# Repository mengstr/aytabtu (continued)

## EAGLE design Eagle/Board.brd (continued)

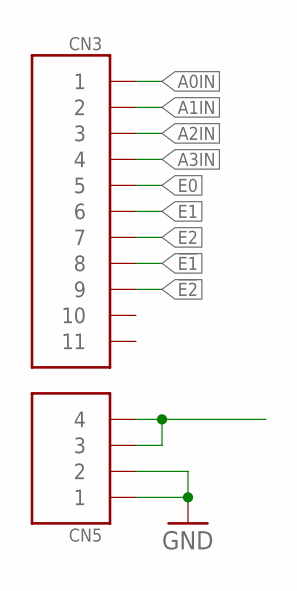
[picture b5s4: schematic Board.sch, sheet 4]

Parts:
CN3: HD11
CN5: HD4

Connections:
!E1: CN3.P$8 (8)
!E2: CN3.P$9 (9)
A0IN: CN3.P$1 (1); also elsewhere on the board
A1IN: CN3.P$2 (2); also elsewhere on the board
A2IN: CN3.P$3 (3); also elsewhere on the board
A3IN: CN3.P$4 (4)
E0: CN3.P$5 (5)
E1: CN3.P$6 (6)
E2: CN3.P$7 (7)
GND: CN5.P$1 (1), CN5.P$2 (2); also elsewhere on the board
unnamed: CN5.P$3 (3), CN5.P$4 (4)

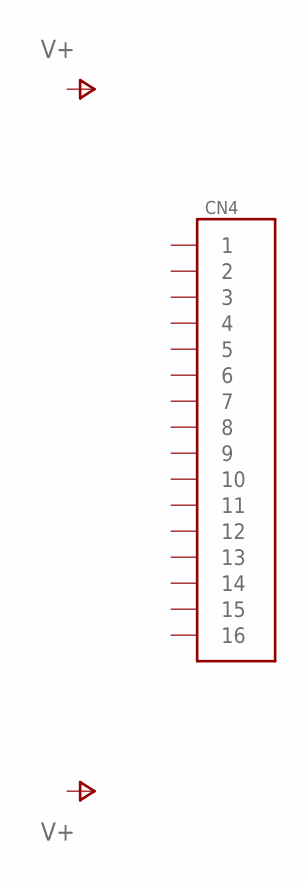
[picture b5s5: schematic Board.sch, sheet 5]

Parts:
CN4: HD16

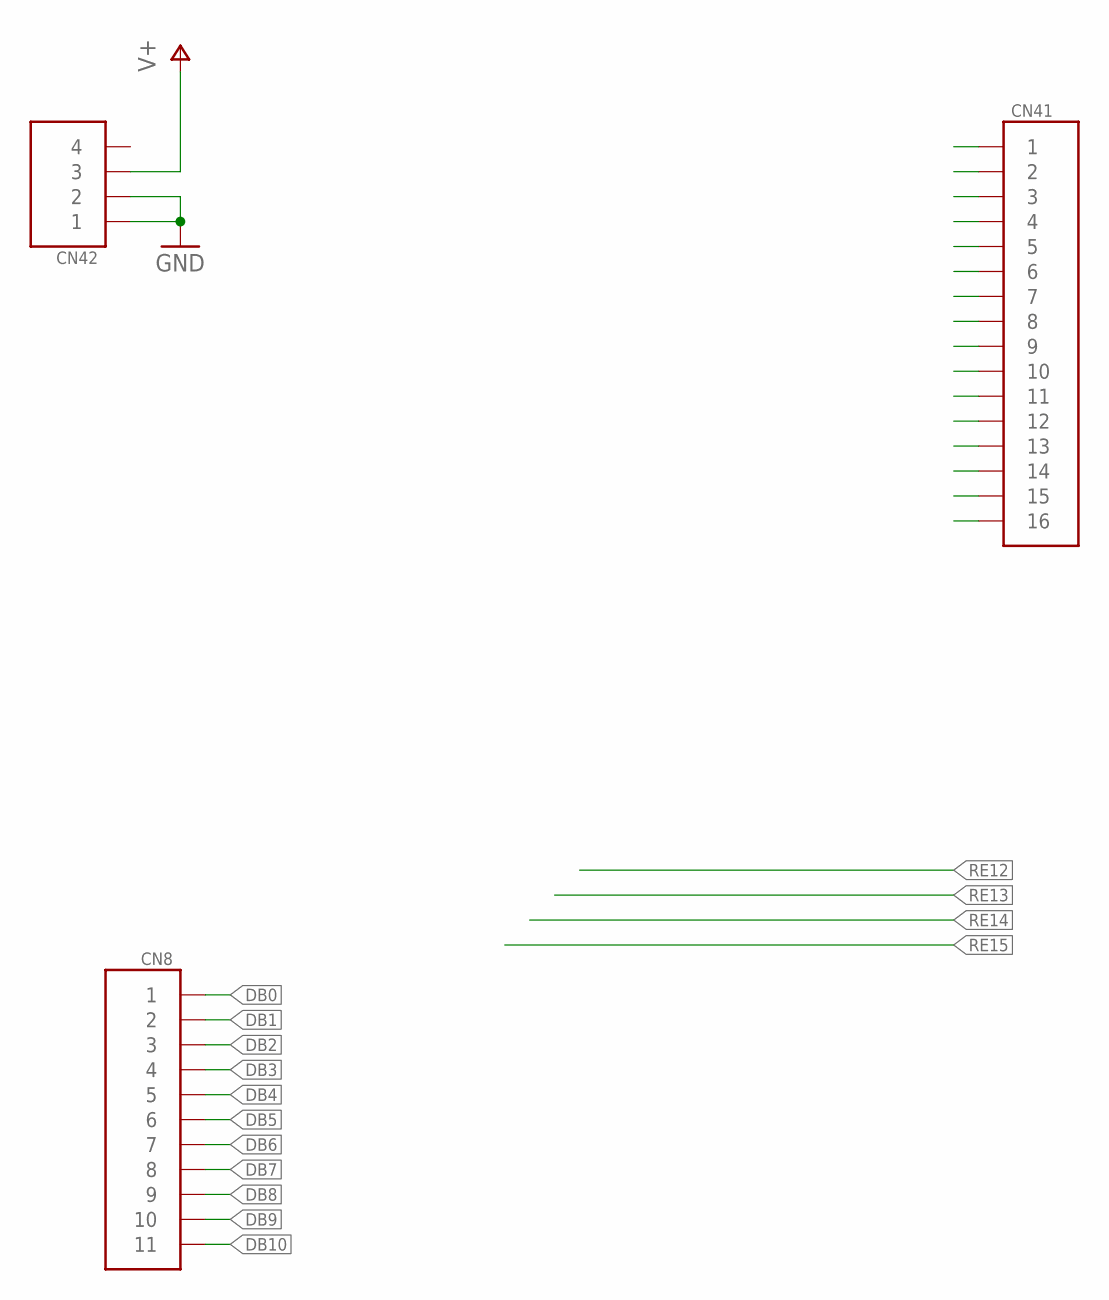
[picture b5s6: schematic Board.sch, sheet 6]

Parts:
CN8: HD11
CN41: HD16
CN42: HD4

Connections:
DB0: CN8.P$1 (1)
DB1: CN8.P$2 (2)
DB2: CN8.P$3 (3)
DB3: CN8.P$4 (4)
DB4: CN8.P$5 (5)
DB5: CN8.P$6 (6)
DB6: CN8.P$7 (7)
DB7: CN8.P$8 (8)
DB8: CN8.P$9 (9)
DB9: CN8.P$10 (10)
DB10: CN8.P$11 (11)
GND: CN42.P$1 (1), CN42.P$2 (2); also elsewhere on the board
SEL16: CN41.P$1 (1)
SEL17: CN41.P$2 (2)
SEL18: CN41.P$3 (3)
SEL19: CN41.P$4 (4)
SEL20: CN41.P$5 (5)
SEL21: CN41.P$6 (6)
SEL22: CN41.P$7 (7)
SEL23: CN41.P$8 (8)
SEL24: CN41.P$9 (9)
SEL25: CN41.P$10 (10)
SEL26: CN41.P$11 (11)
SEL27: CN41.P$12 (12)
SEL28: CN41.P$13 (13)
SEL29: CN41.P$16 (16)
SEL30: CN41.P$15 (15)
SEL31: CN41.P$14 (14)
V+: CN42.P$3 (3); also elsewhere on the board

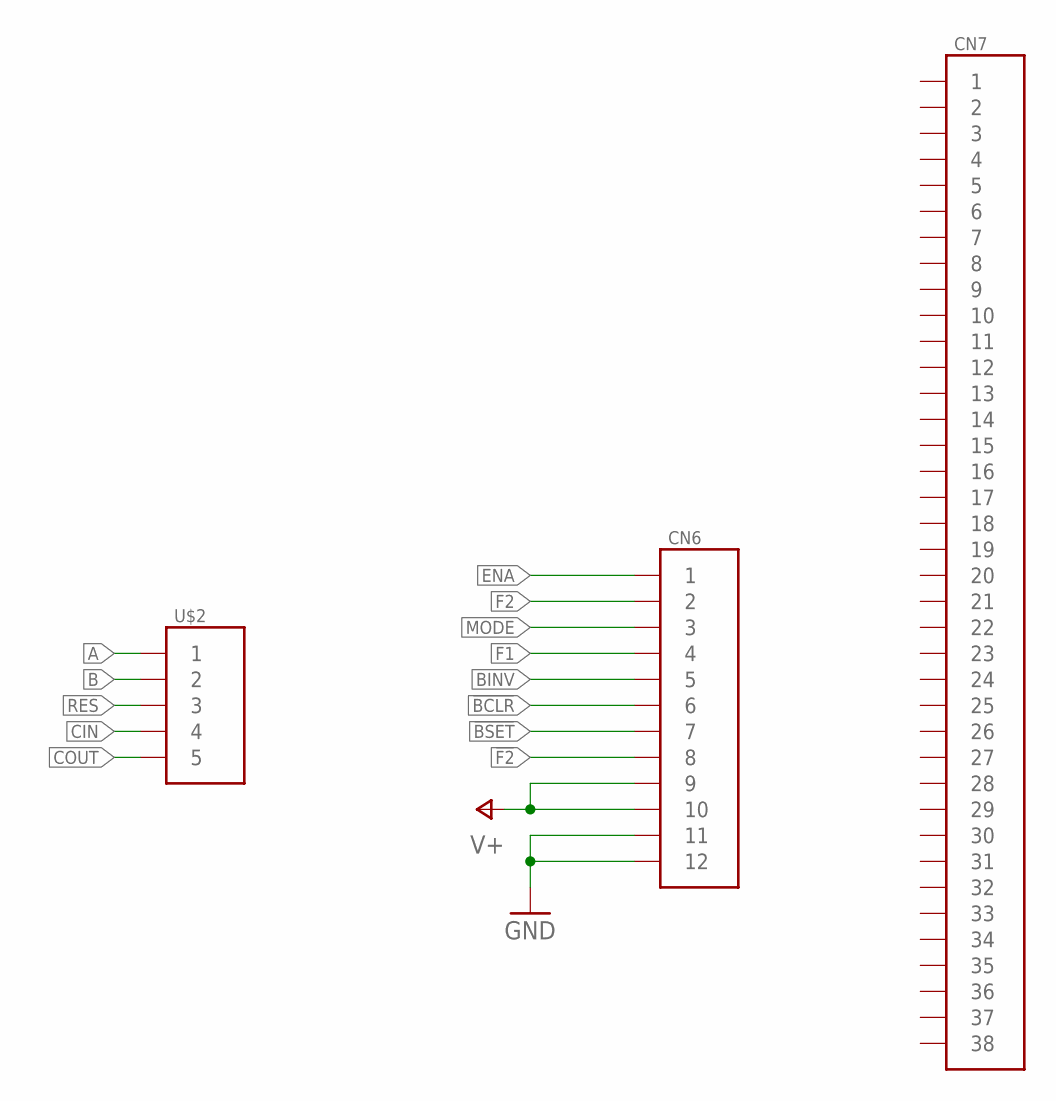
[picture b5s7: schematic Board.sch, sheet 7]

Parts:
CN6: HD12
CN7: HD38-HP; HD38-HOLEPAD
U$2: HD5CN; HD5

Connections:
!BCLR: CN6.P$6 (6)
!BSET: CN6.P$7 (7)
!F2: CN6.P$8 (8)
A: U$2.P$1 (1)
B: U$2.P$2 (2)
BINV: CN6.P$5 (5)
CIN: U$2.P$4 (4)
COUT: U$2.P$5 (5)
ENA: CN6.P$1 (1)
F1: CN6.P$4 (4)
F2: CN6.P$2 (2)
GND: CN6.P$11 (11), CN6.P$12 (12); also elsewhere on the board
MODE: CN6.P$3 (3)
RES: U$2.P$3 (3)
V+: CN6.P$9 (9), CN6.P$10 (10); also elsewhere on the board

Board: 2 copper layers, 15 parts (0 on the bottom side), 8 nets, no tracks yet.

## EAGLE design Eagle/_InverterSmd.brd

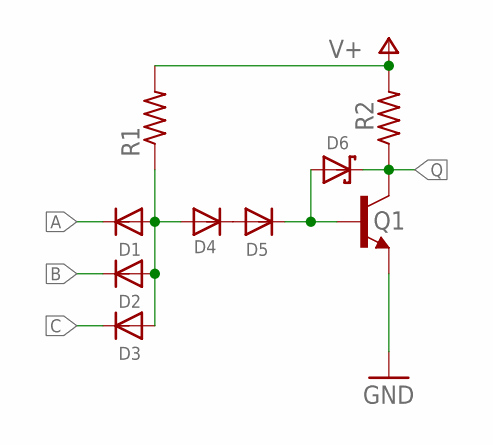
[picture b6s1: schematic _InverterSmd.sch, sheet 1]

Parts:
D1, D2, D3, D4, D5: DIODE-SOD323; SOD323F
D6: SCHOTTKYSOT323; SOT23
Q1: BC547-SOT23; SOT23
R1: 470; R0805
R2: 150; R0805

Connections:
A: D1.C
B: D2.C
C: D3.C
GND: Q1.2 (E)
unnamed: D1.A, D2.A, D3.A, D4.A, R1.1
unnamed: D5.C, D6.1 (A), Q1.1 (B)
unnamed: D4.C, D5.A
Q: D6.3 (C), Q1.3 (C), R2.1
V+: R1.2, R2.2

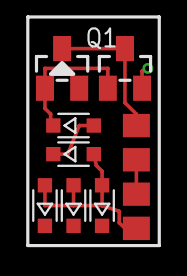
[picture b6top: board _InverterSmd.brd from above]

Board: 2 copper layers, 9 parts (0 on the bottom side), 5 nets.

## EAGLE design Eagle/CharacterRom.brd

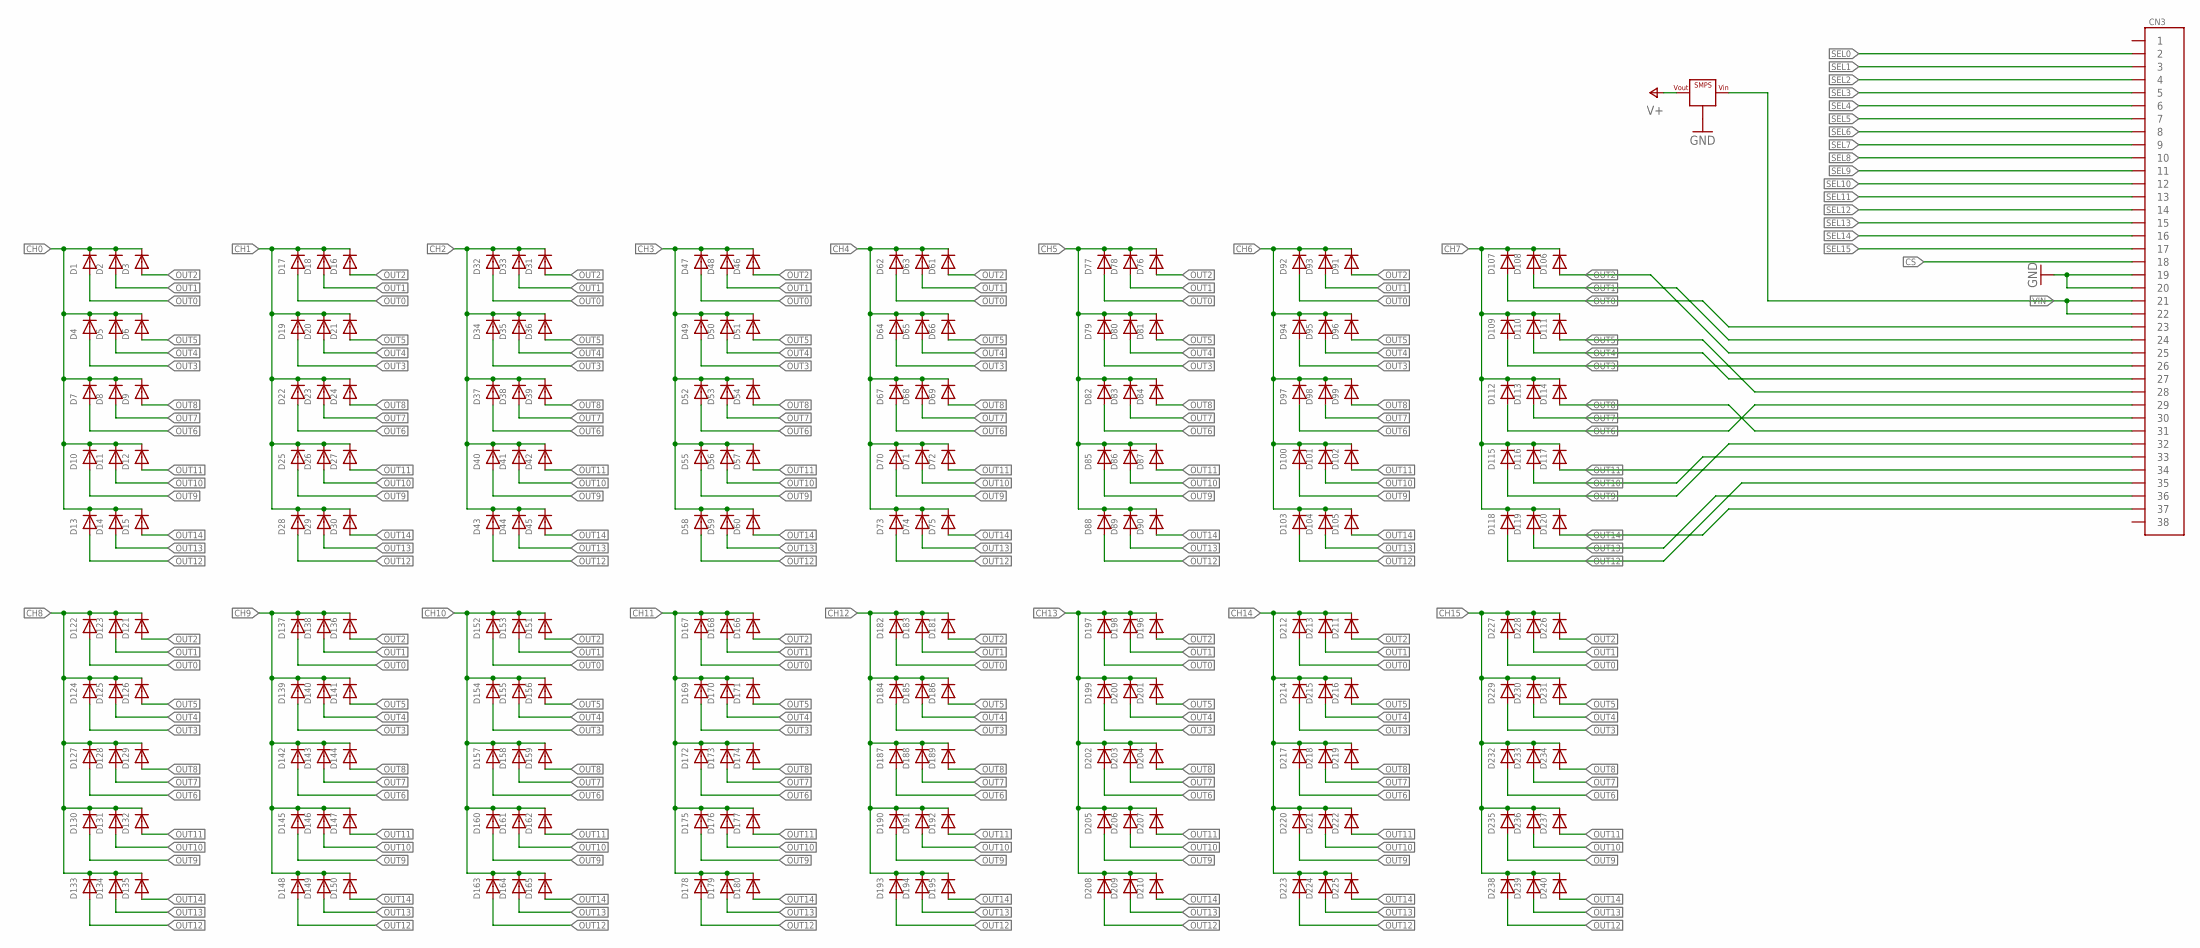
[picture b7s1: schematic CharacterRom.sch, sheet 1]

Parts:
CN3: HD38-HP; HD38-HOLEPAD
D1, D2, D3, D4, D5, D6, D7, D8, D9, D10, D11, D12, D13, D14, D15, D16, D17, D18, D19, D20, D21, D22, D23, D24, D25, D26, D27, D28, D29, D30, D31, D32, D33, D34, D35, D36, D37, D38, D39, D40, D41, D42, D43, D44, D45, D46, D47, D48, D49, D50, D51, D52, D53, D54, D55, D56, D57, D58, D59, D60, D61, D62, D63, D64, D65, D66, D67, D68, D69, D70, D71, D72, D73, D74, D75, D76, D77, D78, D79, D80, D81, D82, D83, D84, D85, D86, D87, D88, D89, D90, D91, D92, D93, D94, D95, D96, D97, D98, D99, D100, D101, D102, D103, D104, D105, D106, D107, D108, D109, D110, D111, D112, D113, D114, D115, D116, D117, D118, D119, D120, D121, D122, D123, D124, D125, D126, D127, D128, D129, D130, D131, D132, D133, D134, D135, D136, D137, D138, D139, D140, D141, D142, D143, D144, D145, D146, D147, D148, D149, D150, D151, D152, D153, D154, D155, D156, D157, D158, D159, D160, D161, D162, D163, D164, D165, D166, D167, D168, D169, D170, D171, D172, D173, D174, D175, D176, D177, D178, D179, D180, D181, D182, D183, D184, D185, D186, D187, D188, D189, D190, D191, D192, D193, D194, D195, D196, D197, D198, D199, D200, D201, D202, D203, D204, D205, D206, D207, D208, D209, D210, D211, D212, D213, D214, D215, D216, D217, D218, D219, D220, D221, D222, D223, D224, D225, D226, D227, D228, D229, D230, D231, D232, D233, D234, D235, D236, D237, D238, D239, D240: DIODESOD-323F; SOD-323F
VR1: SMPS; BUCK1722

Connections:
CH0: D1.C, D2.C, D3.C, D4.C, D5.C, D6.C, D7.C, D8.C, D9.C, D10.C, D11.C, D12.C, D13.C, D14.C, D15.C; also elsewhere on the board
CH1: D16.C, D17.C, D18.C, D19.C, D20.C, D21.C, D22.C, D23.C, D24.C, D25.C, D26.C, D27.C, D28.C, D29.C, D30.C; also elsewhere on the board
CH2: D31.C, D32.C, D33.C, D34.C, D35.C, D36.C, D37.C, D38.C, D39.C, D40.C, D41.C, D42.C, D43.C, D44.C, D45.C; also elsewhere on the board
CH3: D46.C, D47.C, D48.C, D49.C, D50.C, D51.C, D52.C, D53.C, D54.C, D55.C, D56.C, D57.C, D58.C, D59.C, D60.C; also elsewhere on the board
CH4: D61.C, D62.C, D63.C, D64.C, D65.C, D66.C, D67.C, D68.C, D69.C, D70.C, D71.C, D72.C, D73.C, D74.C, D75.C; also elsewhere on the board
CH5: D76.C, D77.C, D78.C, D79.C, D80.C, D81.C, D82.C, D83.C, D84.C, D85.C, D86.C, D87.C, D88.C, D89.C, D90.C; also elsewhere on the board
CH6: D91.C, D92.C, D93.C, D94.C, D95.C, D96.C, D97.C, D98.C, D99.C, D100.C, D101.C, D102.C, D103.C, D104.C, D105.C; also elsewhere on the board
CH7: D106.C, D107.C, D108.C, D109.C, D110.C, D111.C, D112.C, D113.C, D114.C, D115.C, D116.C, D117.C, D118.C, D119.C, D120.C; also elsewhere on the board
CH8: D121.C, D122.C, D123.C, D124.C, D125.C, D126.C, D127.C, D128.C, D129.C, D130.C, D131.C, D132.C, D133.C, D134.C, D135.C; also elsewhere on the board
CH9: D136.C, D137.C, D138.C, D139.C, D140.C, D141.C, D142.C, D143.C, D144.C, D145.C, D146.C, D147.C, D148.C, D149.C, D150.C; also elsewhere on the board
CH10: D151.C, D152.C, D153.C, D154.C, D155.C, D156.C, D157.C, D158.C, D159.C, D160.C, D161.C, D162.C, D163.C, D164.C, D165.C; also elsewhere on the board
CH11: D166.C, D167.C, D168.C, D169.C, D170.C, D171.C, D172.C, D173.C, D174.C, D175.C, D176.C, D177.C, D178.C, D179.C, D180.C; also elsewhere on the board
CH12: D181.C, D182.C, D183.C, D184.C, D185.C, D186.C, D187.C, D188.C, D189.C, D190.C, D191.C, D192.C, D193.C, D194.C, D195.C; also elsewhere on the board
CH13: D196.C, D197.C, D198.C, D199.C, D200.C, D201.C, D202.C, D203.C, D204.C, D205.C, D206.C, D207.C, D208.C, D209.C, D210.C; also elsewhere on the board
CH14: D211.C, D212.C, D213.C, D214.C, D215.C, D216.C, D217.C, D218.C, D219.C, D220.C, D221.C, D222.C, D223.C, D224.C, D225.C; also elsewhere on the board
CH15: D226.C, D227.C, D228.C, D229.C, D230.C, D231.C, D232.C, D233.C, D234.C, D235.C, D236.C, D237.C, D238.C, D239.C, D240.C; also elsewhere on the board
CS: CN3.P18@1 (18), CN3.P18@2 (18); also elsewhere on the board
GND: CN3.P19@1 (19), CN3.P19@2 (19), CN3.P20@1 (20), CN3.P20@2 (20), VR1.GND@1 (GND), VR1.GND@2 (GND), VR1.GND@3 (GND), VR1.GND@4 (GND); also elsewhere on the board
OUT0: CN3.P23@1 (23), CN3.P23@2 (23), D1.A, D17.A, D32.A, D47.A, D62.A, D77.A, D92.A, D107.A, D122.A, D137.A, D152.A, D167.A, D182.A, D197.A, D212.A, D227.A
OUT1: CN3.P24@1 (24), CN3.P24@2 (24), D2.A, D18.A, D33.A, D48.A, D63.A, D78.A, D93.A, D108.A, D123.A, D138.A, D153.A, D168.A, D183.A, D198.A, D213.A, D228.A
OUT2: CN3.P25@1 (25), CN3.P25@2 (25), D3.A, D16.A, D31.A, D46.A, D61.A, D76.A, D91.A, D106.A, D121.A, D136.A, D151.A, D166.A, D181.A, D196.A, D211.A, D226.A
OUT3: CN3.P26@1 (26), CN3.P26@2 (26), D4.A, D19.A, D34.A, D49.A, D64.A, D79.A, D94.A, D109.A, D124.A, D139.A, D154.A, D169.A, D184.A, D199.A, D214.A, D229.A
OUT4: CN3.P27@1 (27), CN3.P27@2 (27), D5.A, D20.A, D35.A, D50.A, D65.A, D80.A, D95.A, D110.A, D125.A, D140.A, D155.A, D170.A, D185.A, D200.A, D215.A, D230.A
OUT5: CN3.P28@1 (28), CN3.P28@2 (28), D6.A, D21.A, D36.A, D51.A, D66.A, D81.A, D96.A, D111.A, D126.A, D141.A, D156.A, D171.A, D186.A, D201.A, D216.A, D231.A
OUT6: CN3.P29@1 (29), CN3.P29@2 (29), D7.A, D22.A, D37.A, D52.A, D67.A, D82.A, D97.A, D112.A, D127.A, D142.A, D157.A, D172.A, D187.A, D202.A, D217.A, D232.A
OUT7: CN3.P30@1 (30), CN3.P30@2 (30), D8.A, D23.A, D38.A, D53.A, D68.A, D83.A, D98.A, D113.A, D128.A, D143.A, D158.A, D173.A, D188.A, D203.A, D218.A, D233.A
OUT8: CN3.P31@1 (31), CN3.P31@2 (31), D9.A, D24.A, D39.A, D54.A, D69.A, D84.A, D99.A, D114.A, D129.A, D144.A, D159.A, D174.A, D189.A, D204.A, D219.A, D234.A
OUT9: CN3.P32@1 (32), CN3.P32@2 (32), D10.A, D25.A, D40.A, D55.A, D70.A, D85.A, D100.A, D115.A, D130.A, D145.A, D160.A, D175.A, D190.A, D205.A, D220.A, D235.A
OUT10: CN3.P33@1 (33), CN3.P33@2 (33), D11.A, D26.A, D41.A, D56.A, D71.A, D86.A, D101.A, D116.A, D131.A, D146.A, D161.A, D176.A, D191.A, D206.A, D221.A, D236.A
OUT11: CN3.P34@1 (34), CN3.P34@2 (34), D12.A, D27.A, D42.A, D57.A, D72.A, D87.A, D102.A, D117.A, D132.A, D147.A, D162.A, D177.A, D192.A, D207.A, D222.A, D237.A
OUT12: CN3.P35@1 (35), CN3.P35@2 (35), D13.A, D28.A, D43.A, D58.A, D73.A, D88.A, D103.A, D118.A, D133.A, D148.A, D163.A, D178.A, D193.A, D208.A, D223.A, D238.A
OUT13: CN3.P36@1 (36), CN3.P36@2 (36), D14.A, D29.A, D44.A, D59.A, D74.A, D89.A, D104.A, D119.A, D134.A, D149.A, D164.A, D179.A, D194.A, D209.A, D224.A, D239.A
OUT14: CN3.P37@1 (37), CN3.P37@2 (37), D15.A, D30.A, D45.A, D60.A, D75.A, D90.A, D105.A, D120.A, D135.A, D150.A, D165.A, D180.A, D195.A, D210.A, D225.A, D240.A
SEL0: CN3.P2@1 (2), CN3.P2@2 (2); also elsewhere on the board
SEL1: CN3.P3@1 (3), CN3.P3@2 (3); also elsewhere on the board
SEL2: CN3.P4@1 (4), CN3.P4@2 (4); also elsewhere on the board
SEL3: CN3.P5@1 (5), CN3.P5@2 (5); also elsewhere on the board
SEL4: CN3.P6@1 (6), CN3.P6@2 (6); also elsewhere on the board
SEL5: CN3.P7@1 (7), CN3.P7@2 (7); also elsewhere on the board
SEL6: CN3.P8@1 (8), CN3.P8@2 (8); also elsewhere on the board
SEL7: CN3.P9@1 (9), CN3.P9@2 (9); also elsewhere on the board
SEL8: CN3.P10@1 (10), CN3.P10@2 (10); also elsewhere on the board
SEL9: CN3.P11@1 (11), CN3.P11@2 (11); also elsewhere on the board
SEL10: CN3.P12@1 (12), CN3.P12@2 (12); also elsewhere on the board
SEL11: CN3.P13@1 (13), CN3.P13@2 (13); also elsewhere on the board
SEL12: CN3.P14@1 (14), CN3.P14@2 (14); also elsewhere on the board
SEL13: CN3.P15@1 (15), CN3.P15@2 (15); also elsewhere on the board
SEL14: CN3.P16@1 (16), CN3.P16@2 (16); also elsewhere on the board
SEL15: CN3.P17@1 (17), CN3.P17@2 (17); also elsewhere on the board
V+: VR1.OUT@1 (VOUT), VR1.OUT@2 (VOUT); also elsewhere on the board
VIN: CN3.P21@1 (21), CN3.P21@2 (21), CN3.P22@1 (22), CN3.P22@2 (22), VR1.IN@1 (VIN), VR1.IN@2 (VIN)

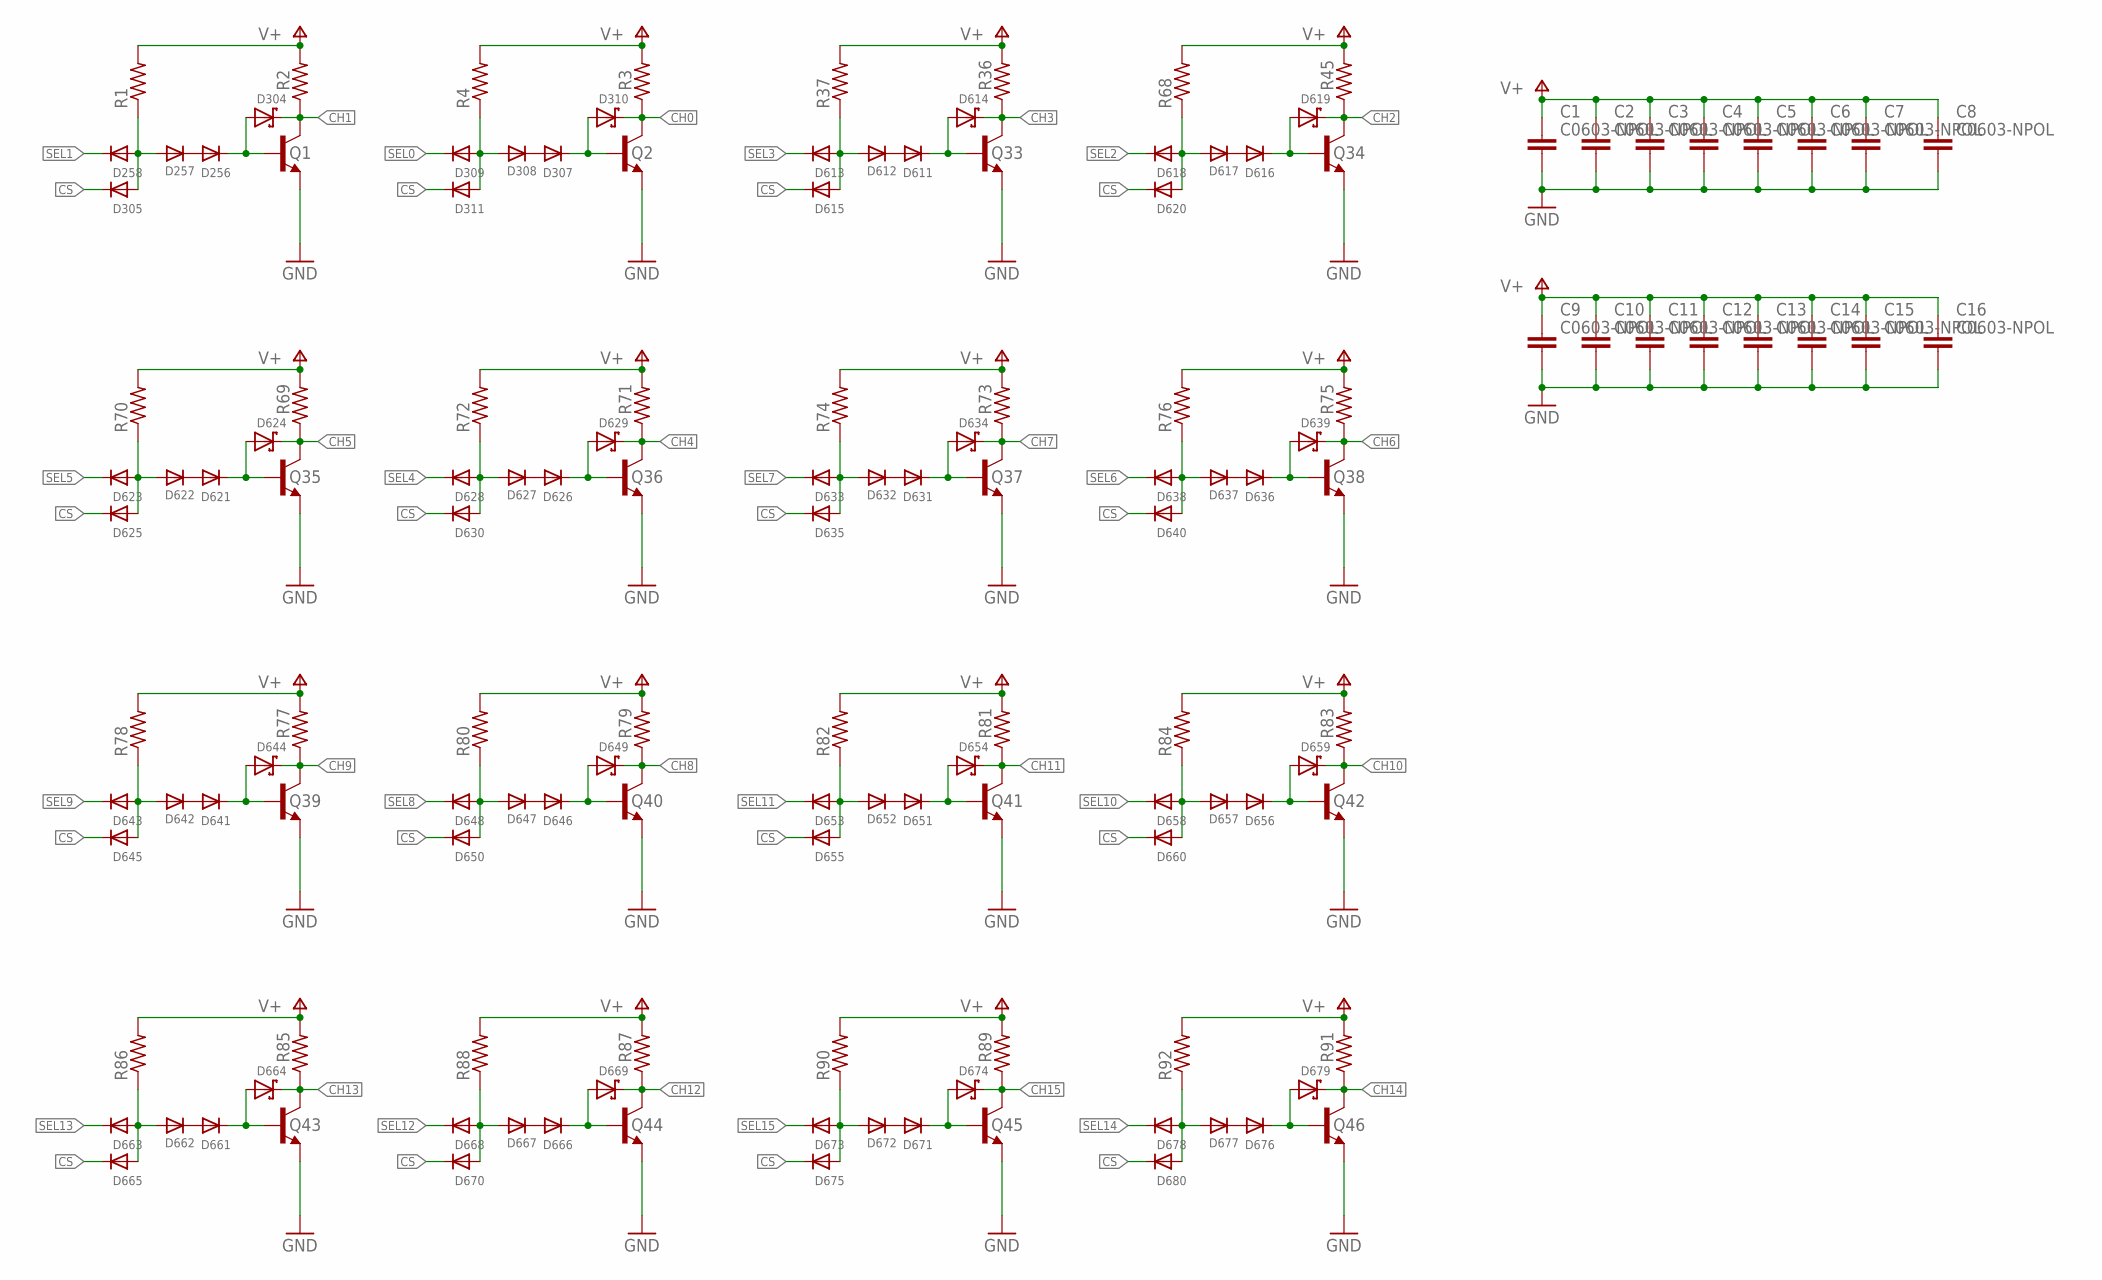
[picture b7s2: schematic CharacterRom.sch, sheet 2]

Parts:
C1, C2, C3, C4, C5, C6, C7, C8, C9, C10, C11, C12, C13, C14, C15, C16: C0603-NPOL; C0603
D256, D257, D258, D305, D307, D308, D309, D311, D611, D612, D613, D615, D616, D617, D618, D620, D621, D622, D623, D625, D626, D627, D628, D630, D631, D632, D633, D635, D636, D637, D638, D640, D641, D642, D643, D645, D646, D647, D648, D650, D651, D652, D653, D655, D656, D657, D658, D660, D661, D662, D663, D665, D666, D667, D668, D670, D671, D672, D673, D675, D676, D677, D678, D680: DIODE-SOD323; SOD323F
D304, D310, D614, D619, D624, D629, D634, D639, D644, D649, D654, D659, D664, D669, D674, D679: SCHOTTKYSOT323; SOT23
Q1, Q2, Q33, Q34, Q35, Q36, Q37, Q38, Q39, Q40, Q41, Q42, Q43, Q44, Q45, Q46: BC547-SOT23; SOT23
R1, R4, R37, R68, R70, R72, R74, R76, R78, R80, R82, R84, R86, R88, R90, R92: 470; R0805
R2, R3, R36, R45, R69, R71, R73, R75, R77, R79, R81, R83, R85, R87, R89, R91: 150; R0805

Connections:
CH0: D310.3 (C), Q2.3 (C), R3.1; also elsewhere on the board
CH1: D304.3 (C), Q1.3 (C), R2.1; also elsewhere on the board
CH2: D619.3 (C), Q34.3 (C), R45.1; also elsewhere on the board
CH3: D614.3 (C), Q33.3 (C), R36.1; also elsewhere on the board
CH4: D629.3 (C), Q36.3 (C), R71.1; also elsewhere on the board
CH5: D624.3 (C), Q35.3 (C), R69.1; also elsewhere on the board
CH6: D639.3 (C), Q38.3 (C), R75.1; also elsewhere on the board
CH7: D634.3 (C), Q37.3 (C), R73.1; also elsewhere on the board
CH8: D649.3 (C), Q40.3 (C), R79.1; also elsewhere on the board
CH9: D644.3 (C), Q39.3 (C), R77.1; also elsewhere on the board
CH10: D659.3 (C), Q42.3 (C), R83.1; also elsewhere on the board
CH11: D654.3 (C), Q41.3 (C), R81.1; also elsewhere on the board
CH12: D669.3 (C), Q44.3 (C), R87.1; also elsewhere on the board
CH13: D664.3 (C), Q43.3 (C), R85.1; also elsewhere on the board
CH14: D679.3 (C), Q46.3 (C), R91.1; also elsewhere on the board
CH15: D674.3 (C), Q45.3 (C), R89.1; also elsewhere on the board
CS: D305.C, D311.C, D615.C, D620.C, D625.C, D630.C, D635.C, D640.C, D645.C, D650.C, D655.C, D660.C, D665.C, D670.C, D675.C, D680.C; also elsewhere on the board
GND: C1.2, C2.2, C3.2, C4.2, C5.2, C6.2, C7.2, C8.2, C9.2, C10.2, C11.2, C12.2, C13.2, C14.2, C15.2, C16.2, Q1.2 (E), Q2.2 (E), Q33.2 (E), Q34.2 (E), Q35.2 (E), Q36.2 (E), Q37.2 (E), Q38.2 (E), Q39.2 (E), Q40.2 (E), Q41.2 (E), Q42.2 (E), Q43.2 (E), Q44.2 (E), Q45.2 (E), Q46.2 (E); also elsewhere on the board
unnamed: D256.C, D304.1 (A), Q1.1 (B)
unnamed: D256.A, D257.C
unnamed: D257.A, D258.A, D305.A, R1.1
unnamed: D307.C, D310.1 (A), Q2.1 (B)
unnamed: D307.A, D308.C
unnamed: D308.A, D309.A, D311.A, R4.1
unnamed: D611.C, D614.1 (A), Q33.1 (B)
unnamed: D611.A, D612.C
unnamed: D612.A, D613.A, D615.A, R37.1
unnamed: D616.C, D619.1 (A), Q34.1 (B)
unnamed: D616.A, D617.C
unnamed: D617.A, D618.A, D620.A, R68.1
unnamed: D621.C, D624.1 (A), Q35.1 (B)
unnamed: D621.A, D622.C
unnamed: D622.A, D623.A, D625.A, R70.1
unnamed: D626.C, D629.1 (A), Q36.1 (B)
unnamed: D626.A, D627.C
unnamed: D627.A, D628.A, D630.A, R72.1
unnamed: D631.C, D634.1 (A), Q37.1 (B)
unnamed: D631.A, D632.C
unnamed: D632.A, D633.A, D635.A, R74.1
unnamed: D636.C, D639.1 (A), Q38.1 (B)
unnamed: D636.A, D637.C
unnamed: D637.A, D638.A, D640.A, R76.1
unnamed: D641.C, D644.1 (A), Q39.1 (B)
unnamed: D641.A, D642.C
unnamed: D642.A, D643.A, D645.A, R78.1
unnamed: D646.C, D649.1 (A), Q40.1 (B)
unnamed: D646.A, D647.C
unnamed: D647.A, D648.A, D650.A, R80.1
unnamed: D651.C, D654.1 (A), Q41.1 (B)
unnamed: D651.A, D652.C
unnamed: D652.A, D653.A, D655.A, R82.1
unnamed: D656.C, D659.1 (A), Q42.1 (B)
unnamed: D656.A, D657.C
unnamed: D657.A, D658.A, D660.A, R84.1
unnamed: D661.C, D664.1 (A), Q43.1 (B)
unnamed: D661.A, D662.C
unnamed: D662.A, D663.A, D665.A, R86.1
unnamed: D666.C, D669.1 (A), Q44.1 (B)
unnamed: D666.A, D667.C
unnamed: D667.A, D668.A, D670.A, R88.1
unnamed: D671.C, D674.1 (A), Q45.1 (B)
unnamed: D671.A, D672.C
unnamed: D672.A, D673.A, D675.A, R90.1
unnamed: D676.C, D679.1 (A), Q46.1 (B)
unnamed: D676.A, D677.C
unnamed: D677.A, D678.A, D680.A, R92.1
SEL0: D309.C; also elsewhere on the board
SEL1: D258.C; also elsewhere on the board
SEL2: D618.C; also elsewhere on the board
SEL3: D613.C; also elsewhere on the board
SEL4: D628.C; also elsewhere on the board
SEL5: D623.C; also elsewhere on the board
SEL6: D638.C; also elsewhere on the board
SEL7: D633.C; also elsewhere on the board
SEL8: D648.C; also elsewhere on the board
SEL9: D643.C; also elsewhere on the board
SEL10: D658.C; also elsewhere on the board
SEL11: D653.C; also elsewhere on the board
SEL12: D668.C; also elsewhere on the board
SEL13: D663.C; also elsewhere on the board
SEL14: D678.C; also elsewhere on the board
SEL15: D673.C; also elsewhere on the board
V+: C1.1, C2.1, C3.1, C4.1, C5.1, C6.1, C7.1, C8.1, C9.1, C10.1, C11.1, C12.1, C13.1, C14.1, C15.1, C16.1, R1.2, R2.2, R3.2, R4.2, R36.2, R37.2, R45.2, R68.2, R69.2, R70.2, R71.2, R72.2, R73.2, R74.2, R75.2, R76.2, R77.2, R78.2, R79.2, R80.2, R81.2, R82.2, R83.2, R84.2, R85.2, R86.2, R87.2, R88.2, R89.2, R90.2, R91.2, R92.2; also elsewhere on the board

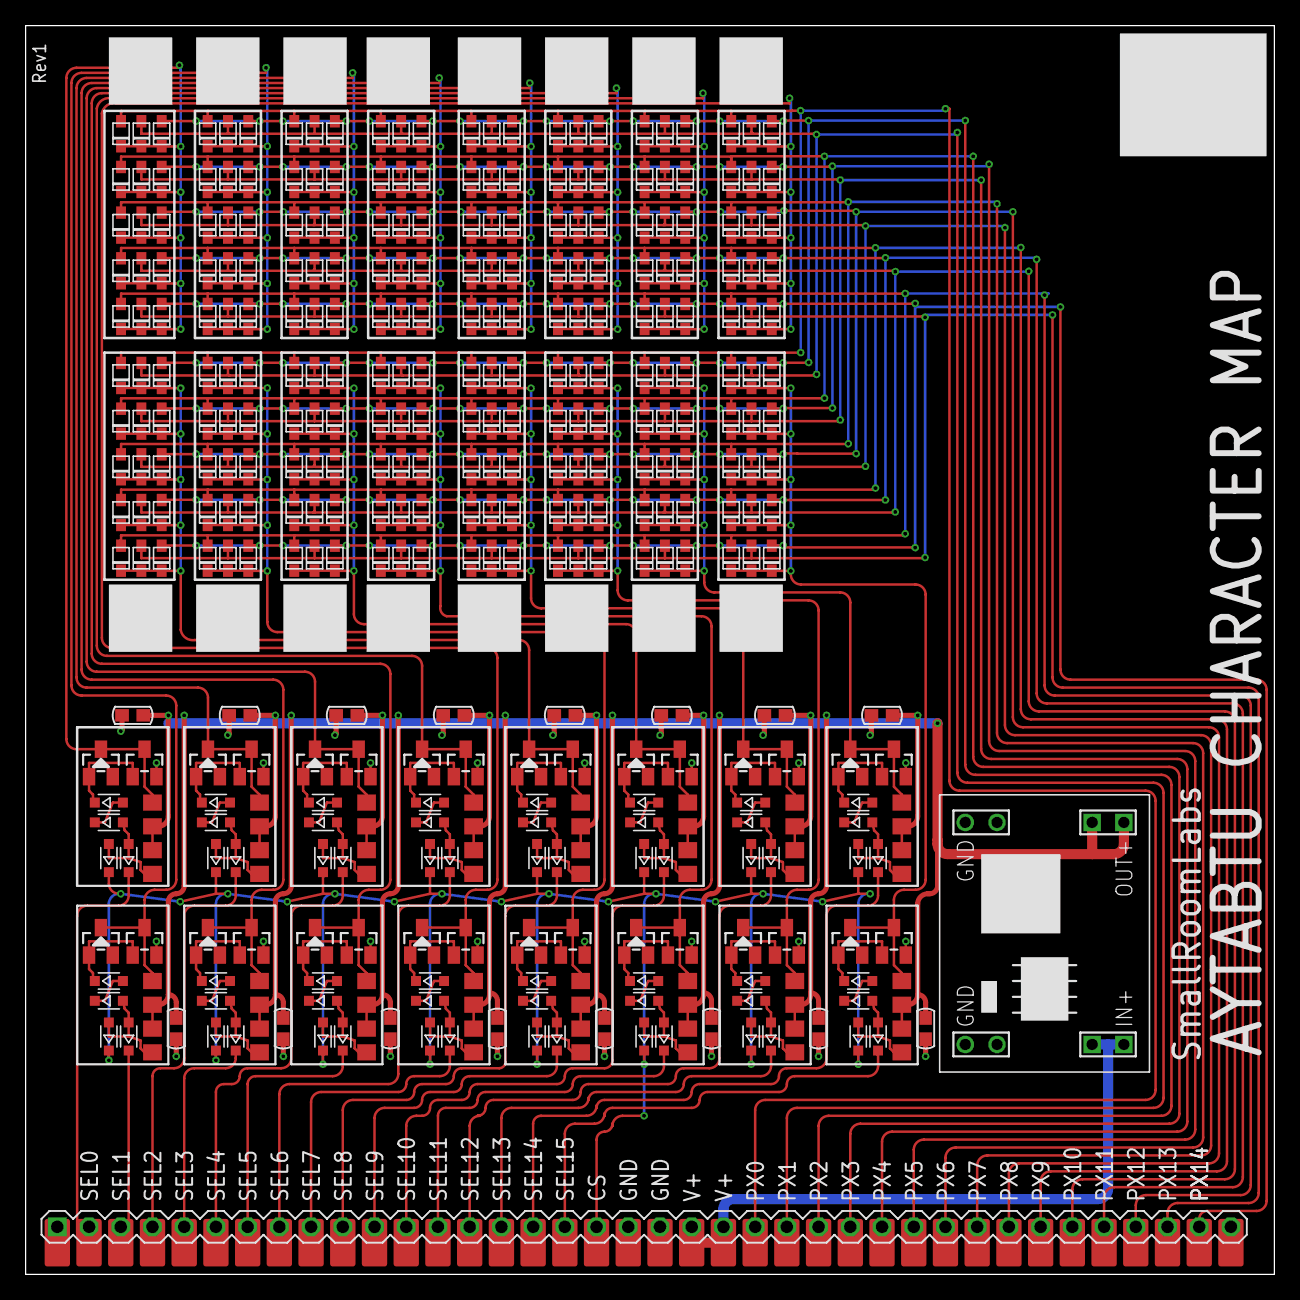
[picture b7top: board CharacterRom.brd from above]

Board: 2 copper layers, 100.0 x 100.0 mm, 386 parts (0 on the bottom side), 99 nets.

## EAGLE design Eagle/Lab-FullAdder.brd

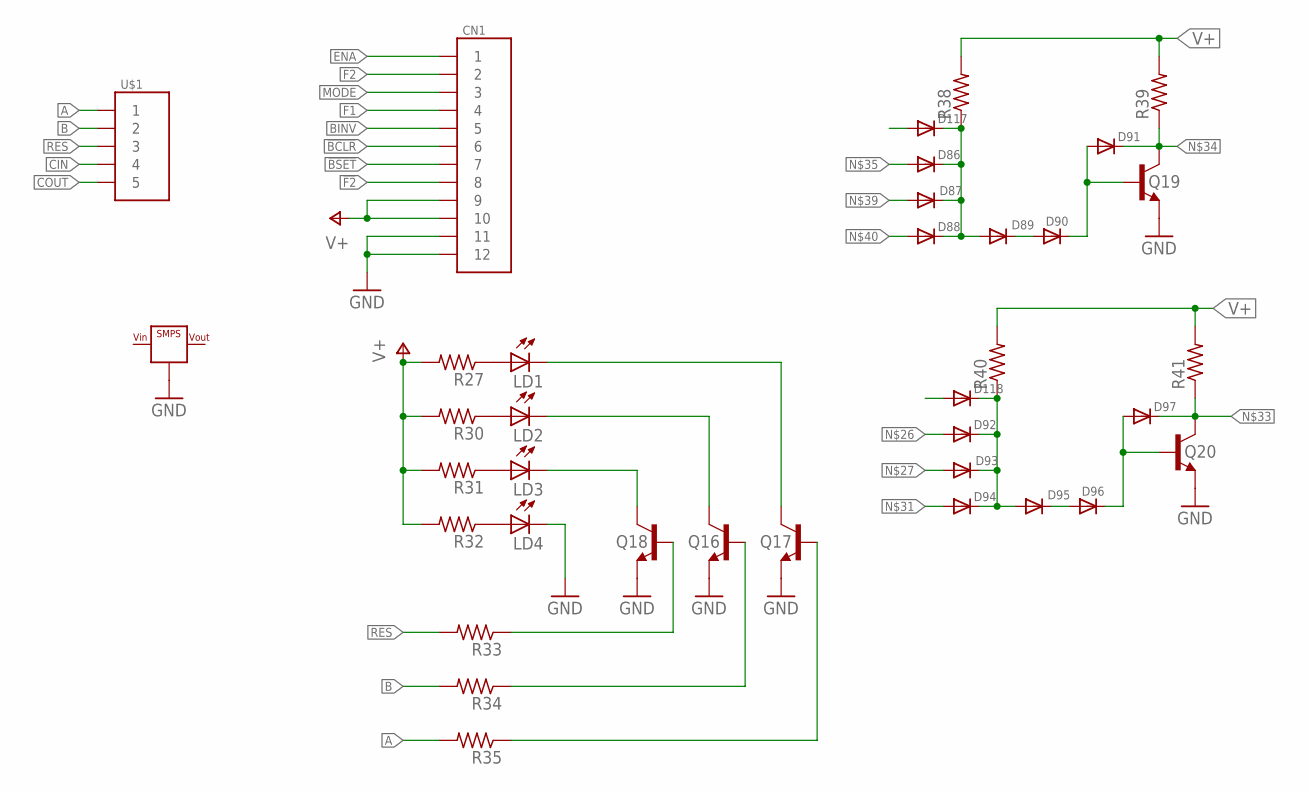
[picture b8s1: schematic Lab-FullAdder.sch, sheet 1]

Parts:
CN1: HD12
D86, D87, D88, D89, D90, D92, D93, D94, D95, D96, D117, D118: DIODE-6.3; DO35-6.3
D91, D97: DIODE-7.6; DO35-7.6
LD1, LD2, LD3, LD4: LED-RA; 3MMRA
Q16, Q17, Q18, Q19, Q20: 2N3904-1; TO92BH
R27, R30, R31, R32, R33, R34, R35, R38, R39, R40, R41: R1/8-7.6MM; R0125-7.6
U$1: HD5CN; HD5
VR1: SMPS; BUCK1722

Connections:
!BCLR: CN1.P$6 (6); also elsewhere on the board
!BSET: CN1.P$7 (7); also elsewhere on the board
!F2: CN1.P$8 (8); also elsewhere on the board
A: R35.2, U$1.P$1 (1); also elsewhere on the board
B: R34.2, U$1.P$2 (2); also elsewhere on the board
BINV: CN1.P$5 (5); also elsewhere on the board
CIN: U$1.P$4 (4); also elsewhere on the board
COUT: U$1.P$5 (5); also elsewhere on the board
ENA: CN1.P$1 (1); also elsewhere on the board
F1: CN1.P$4 (4); also elsewhere on the board
F2: CN1.P$2 (2); also elsewhere on the board
GND: CN1.P$11 (11), CN1.P$12 (12), LD4.C, Q16.1 (E), Q17.1 (E), Q18.1 (E), Q19.1 (E), Q20.1 (E), VR1.GND@1 (GND), VR1.GND@2 (GND), VR1.GND@3 (GND), VR1.GND@4 (GND); also elsewhere on the board
MODE: CN1.P$3 (3); also elsewhere on the board
unnamed: LD1.A, R27.1
unnamed: LD2.A, R30.1
unnamed: LD3.A, R31.1
unnamed: LD4.A, R32.1
unnamed: LD3.C, Q18.3 (C)
unnamed: LD2.C, Q16.3 (C)
unnamed: LD1.C, Q17.3 (C)
unnamed: Q18.2 (B), R33.1
unnamed: Q16.2 (B), R34.1
unnamed: Q17.2 (B), R35.1
unnamed: D97.C, Q20.3 (C), R41.1
unnamed: D91.C, Q19.3 (C), R39.1
unnamed: D86.C, D87.C, D88.C, D89.A, D117.C, R38.1
unnamed: D89.C, D90.A
unnamed: D90.C, D91.A, Q19.2 (B)
unnamed: D92.C, D93.C, D94.C, D95.A, D118.C, R40.1
unnamed: D95.C, D96.A
unnamed: D96.C, D97.A, Q20.2 (B)
RES: R33.2, U$1.P$3 (3); also elsewhere on the board
V+: CN1.P$9 (9), CN1.P$10 (10), R27.2, R30.2, R31.2, R32.2, R38.2, R39.2, R40.2, R41.2; also elsewhere on the board
VIN: VR1.IN@1 (VIN), VR1.IN@2 (VIN)
VOUT: VR1.OUT@1 (VOUT), VR1.OUT@2 (VOUT)
